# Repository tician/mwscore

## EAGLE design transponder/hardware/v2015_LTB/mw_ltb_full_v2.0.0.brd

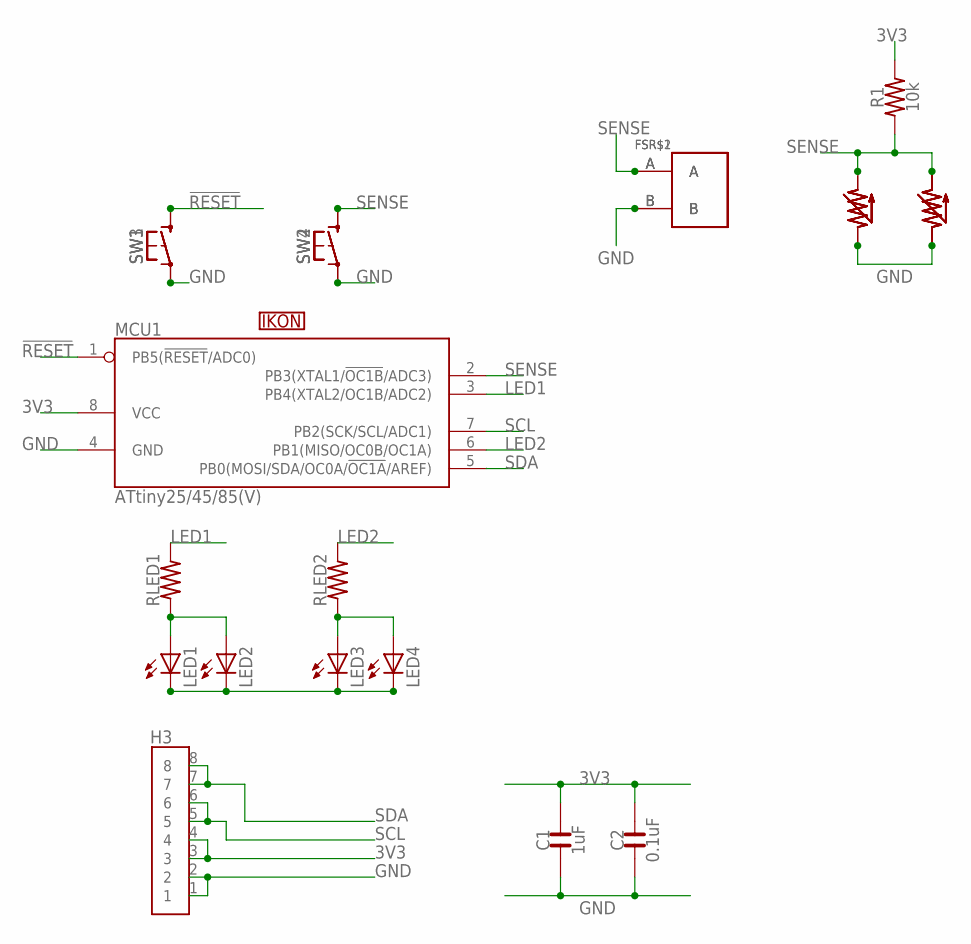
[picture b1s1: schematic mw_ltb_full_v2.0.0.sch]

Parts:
C1: 1uF; 0603_YAGEO
C2: 0.1uF; 0603_YAGEO
FSR$1, FSR$2: FSR_PAD88X44_P2B; FSR_PAD_88X44_P2B
H3: HEADER_8P-0.1"_2X4-SMD-SULLINS; HEADER-0.1"_2X4-SMD-SULLINS
LED1, LED2, LED3, LED4: LED-ZBEND_RM; Z-BEND_RM
MCU1: ATMEL_ATTINY25/45/85(V)-SOIC_DUAL; SOIC-8_DUAL
R1: 10k; 0603_YAGEO
RLED1, RLED2: RESISTOR-0603; 0603_YAGEO
SW1, SW2: SWITCH_SPST-KMT0; SWITCH_KMT0
SW3, SW4: SWITCH_SPST-TL3315; SWITCH_TL3315
U$1, U$3, U$9, U$10: FSR_PINS; FSR_0.1"-PITCH_PADS-0.05"X0.5"
U$2, U$4, U$5, U$6: FSR_PLACE; FSR_1.5[IN]_SQR
U$11: IKONLEARNING-20MIL; IKON_LEARNING_20MIL

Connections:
3V3: C1.2, C2.2, H3.3, H3.4, MCU1.8 (VCC), R1.2
!RESET: MCU1.1 (PB5(!RESET!/ADC0)), SW1.1@1 (1), SW1.1@2 (1), SW3.1@1 (1), SW3.1@2 (1)
GND: C1.1, C2.1, FSR$1.B, FSR$2.B, H3.1, H3.2, LED1.K (C), LED2.K (C), LED3.K (C), LED4.K (C), MCU1.4 (GND), SW1.2@1 (2), SW1.2@2 (2), SW2.2@1 (2), SW2.2@2 (2), SW3.2@1 (2), SW3.2@2 (2), SW4.2@1 (2), SW4.2@2 (2), U$1.P$1, U$3.P$2, U$9.P$2, U$10.P$1
LED1: MCU1.3 (PB4(XTAL2/OC1B/ADC2)), RLED1.2
LED2: MCU1.6 (PB1(MISO/OC0B/OC1A)), RLED2.2
unnamed: LED1.A, LED2.A, RLED1.1
unnamed: LED3.A, LED4.A, RLED2.1
SCL: H3.5, H3.6, MCU1.7 (PB2(SCK/SCL/ADC1))
SDA: H3.7, H3.8, MCU1.5 (PB0(MOSI/SDA/OC0A/!OC1A!/AREF))
SENSE: FSR$1.A, FSR$2.A, MCU1.2 (PB3(XTAL1/!OC1B!/ADC3)), R1.1, SW2.1@1 (1), SW2.1@2 (1), SW4.1@1 (1), SW4.1@2 (1), U$1.P$2, U$3.P$1, U$9.P$1, U$10.P$2

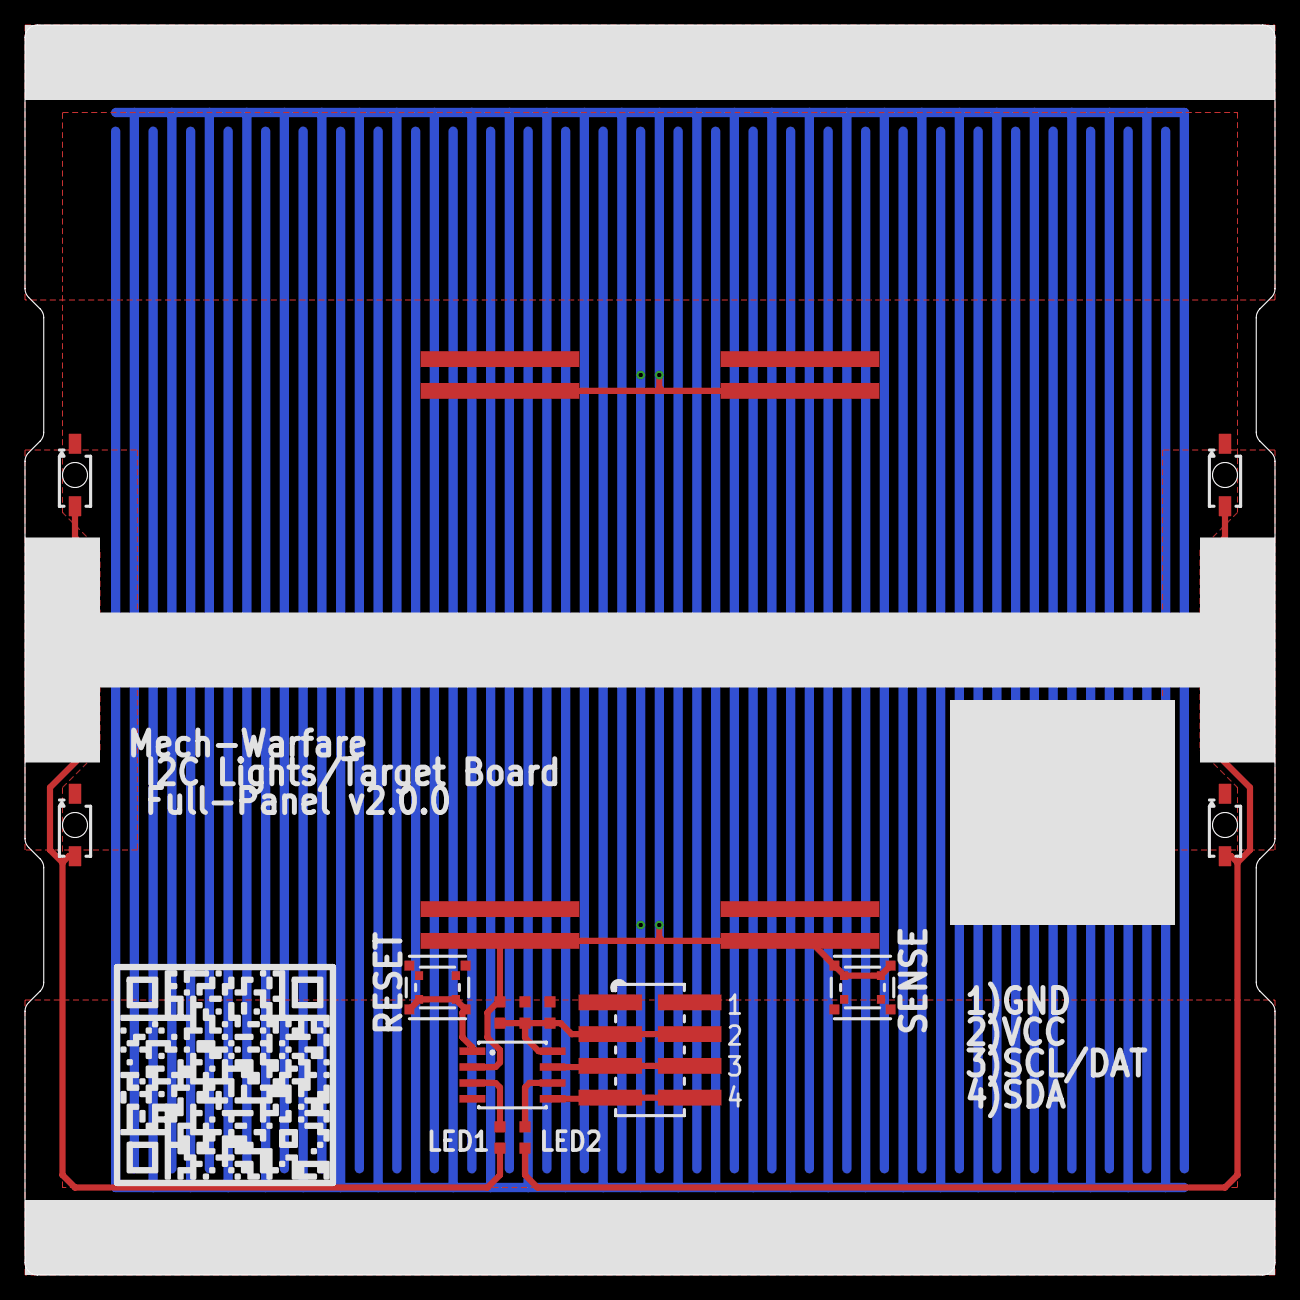
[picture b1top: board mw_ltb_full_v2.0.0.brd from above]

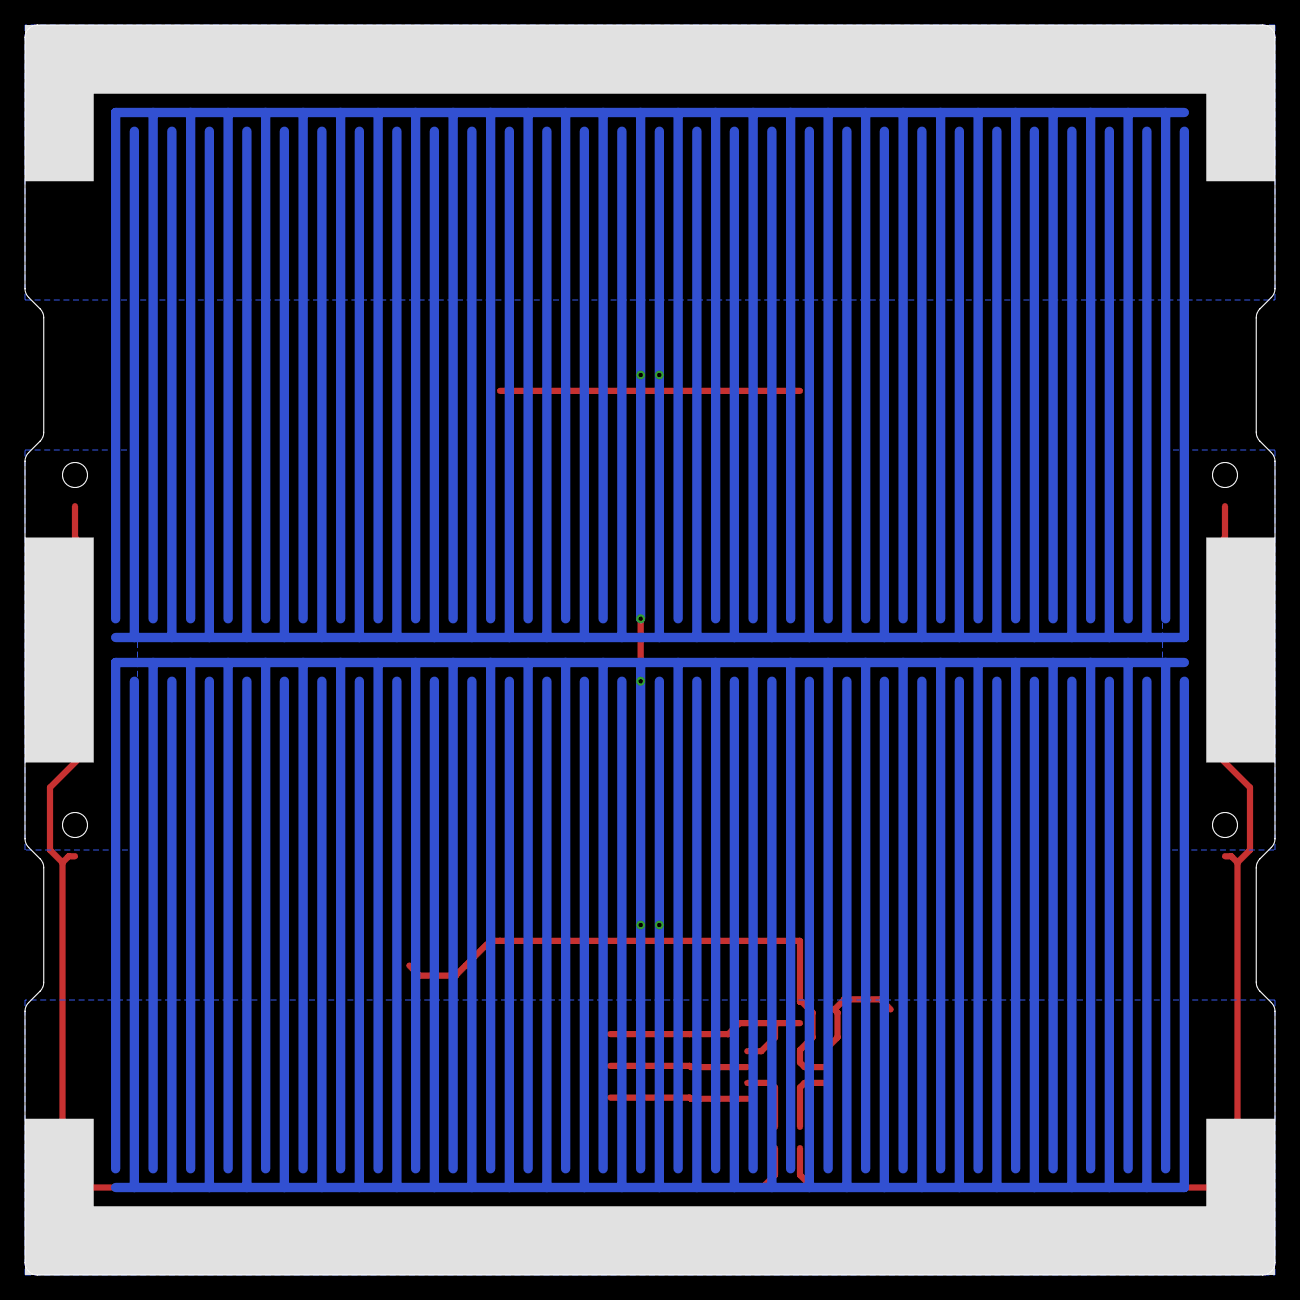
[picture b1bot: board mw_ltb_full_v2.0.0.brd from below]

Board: 2 copper layers, 100.0 x 100.0 mm, 26 parts (4 on the bottom side), 10 nets.

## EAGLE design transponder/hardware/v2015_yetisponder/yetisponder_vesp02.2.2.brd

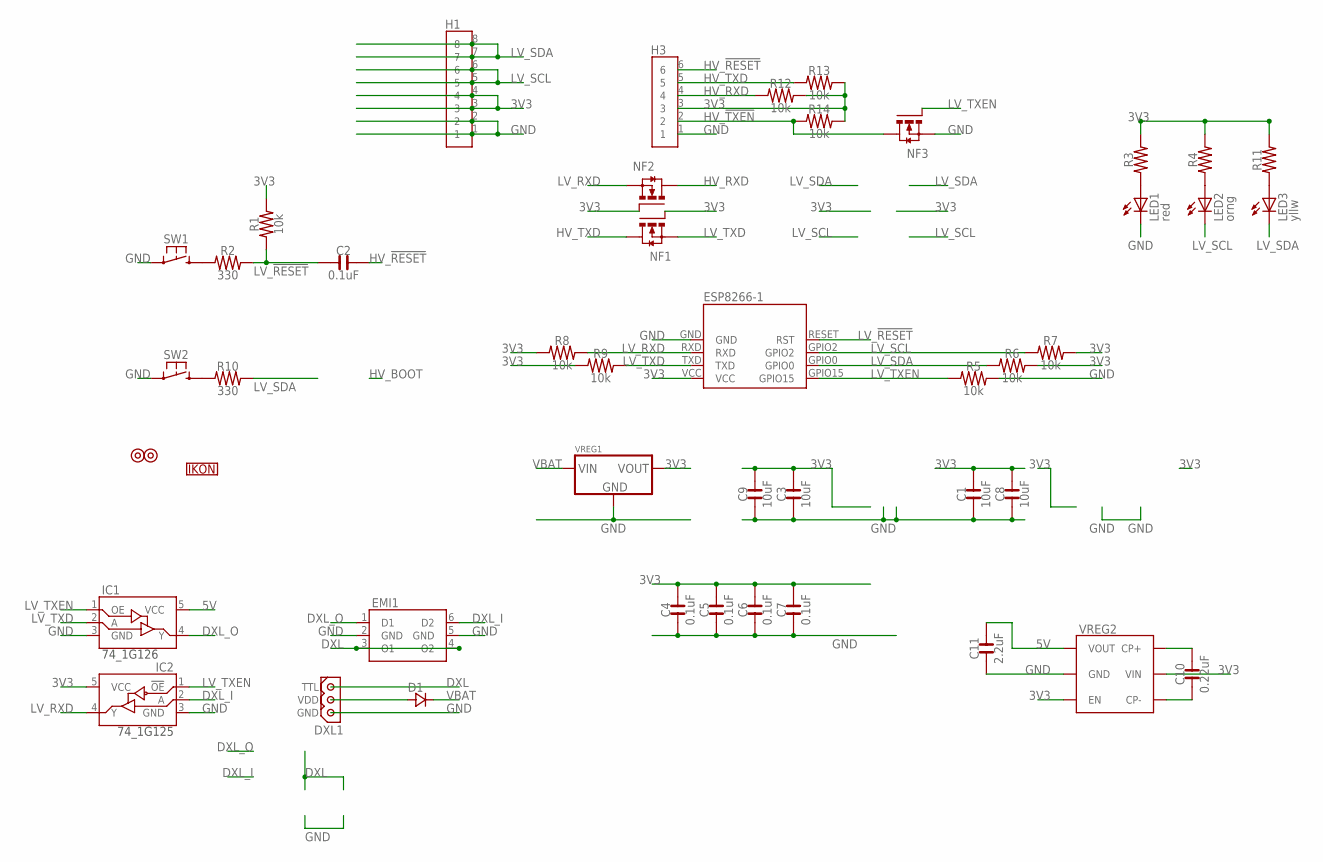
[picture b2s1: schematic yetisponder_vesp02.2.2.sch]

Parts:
C1, C3, C8, C9: 10uF; 0805_YAGEO
C2, C4, C5, C6, C7: 0.1uF; 0402_YAGEO
C10: 0.22uF; 0402_YAGEO
C11: 2.2uF; 0402_YAGEO
D1: DIODE_RECTIFIER-POWER-DI5; POWER-DI5
DXL1: DXL_TTL-V; MOLEX_5267-3
EMI1: EMI_2CH; SOT-563
ESP8266-1: ESP8266-02
H1: HEADER_8P-0.1"_2X4-SMD-SULLINS; HEADER-0.1"_2X4-SMD-SULLINS
H3: HEADER_6P-0.1"; HEADER-0.1"_1X6
IC1: LOGIC_74_1G126-DCK; DCK(R-PDSO-G5)_SC70
IC2: LOGIC_74_1G125-DCK; DCK(R-PDSO-G5)_SC70
IKON1: IKON-VERSACOMA-5; IKON_VERSACOMA_5MM
LED1: red; 0402_LED
LED2: orng; 0402_LED
LED3: yllw; 0402_LED
NF1, NF2, NF3: FET_N-CH-SOT-23-3; SOT-23-3
R1, R5, R6, R7, R8, R9, R12, R13, R14: 10k; 0402_YAGEO
R2, R10: 330; 0402_YAGEO
R3, R4, R11: RESISTOR-0402; 0402_YAGEO
S1, S2: METRIC_SCREWS-M2.5_T; M2.5_SCREW_TENTED
SW1, SW2: SWITCH_SPST-6MMX6MM-PTH; SWITCH_TE_1825910-7
VREG1: VREG_78XX-OKI-78SR-H; VREG-OKI-78SR-H
VREG2: VREG_REG710XX; SOT-23-6

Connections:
3V3: C1.2, C3.2, C4.2, C5.2, C6.2, C7.2, C8.2, C9.2, ESP8266-1.VCC, H1.3, H1.4, H3.3, IC2.5 (VCC), NF1.1G (G), NF2.1G (G), R1.2, R3.2, R4.2, R6.2, R7.2, R8.1, R9.1, R11.2, R12.2, R13.2, R14.2, VREG1.3 (VOUT), VREG2.3 (EN), VREG2.5 (VIN)
5V: C11.2, IC1.5 (VCC), VREG2.1 (VOUT)
DXL: DXL1.1 (TTL), EMI1.3 (O1), EMI1.4 (O2)
DXL_I: EMI1.6 (D2), IC2.2 (A)
DXL_O: EMI1.1 (D1), IC1.4 (Y)
GND: C1.1, C3.1, C4.1, C5.1, C6.1, C7.1, C8.1, C9.1, C11.1, DXL1.3 (GND), EMI1.2 (GND), EMI1.5 (GND), ESP8266-1.GND, H1.1, H1.2, H3.1, IC1.3 (GND), IC2.3 (GND), LED1.C, NF3.2S (S), R5.2, SW1.2@1 (2), SW1.2@2 (2), SW2.2@1 (2), SW2.2@2 (2), VREG1.2 (GND), VREG2.2 (GND)
HV_!RESET!: C2.2, H3.6
HV_!TXEN!: H3.2, NF3.3D (D), R14.1
HV_RXD: H3.4, NF2.3D (D), R12.1
HV_TXD: H3.5, NF1.3D (D), R13.1
LV_!RESET!: C2.1, ESP8266-1.RESET (RST), R1.1, R2.2
LV_RXD: ESP8266-1.RXD, IC2.4 (Y), NF2.2S (S), R8.2
LV_SCL: ESP8266-1.GPIO2, H1.5, H1.6, LED2.C, R7.1
LV_SDA: ESP8266-1.GPIO0, H1.7, H1.8, LED3.C, R6.1, R10.2
LV_TXD: ESP8266-1.TXD, IC1.2 (A), NF1.2S (S), R9.2
LV_TXEN: ESP8266-1.GPIO15, IC1.1 (OE), IC2.1 (!OE!), NF3.1G (G), R5.1
unnamed: R10.1, SW2.1@1 (1), SW2.1@2 (1)
unnamed: LED3.A, R11.1
unnamed: C10.2, VREG2.6 (CP+)
unnamed: D1.LEFT (A), D1.RIGHT (A), DXL1.2 (VDD)
unnamed: LED1.A, R3.1
unnamed: R2.1, SW1.1@1 (1), SW1.1@2 (1)
unnamed: LED2.A, R4.1
unnamed: C10.1, VREG2.4 (CP-)
VBAT: D1.PAD (C), VREG1.1 (VIN)

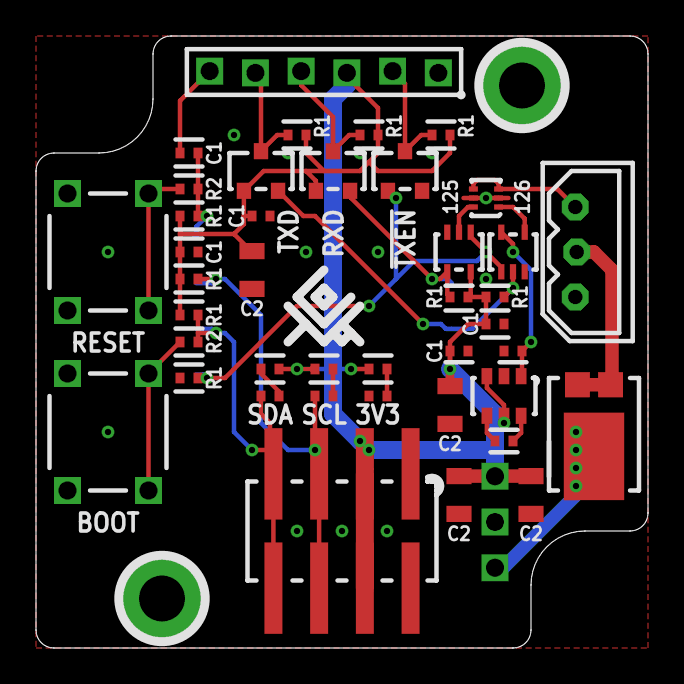
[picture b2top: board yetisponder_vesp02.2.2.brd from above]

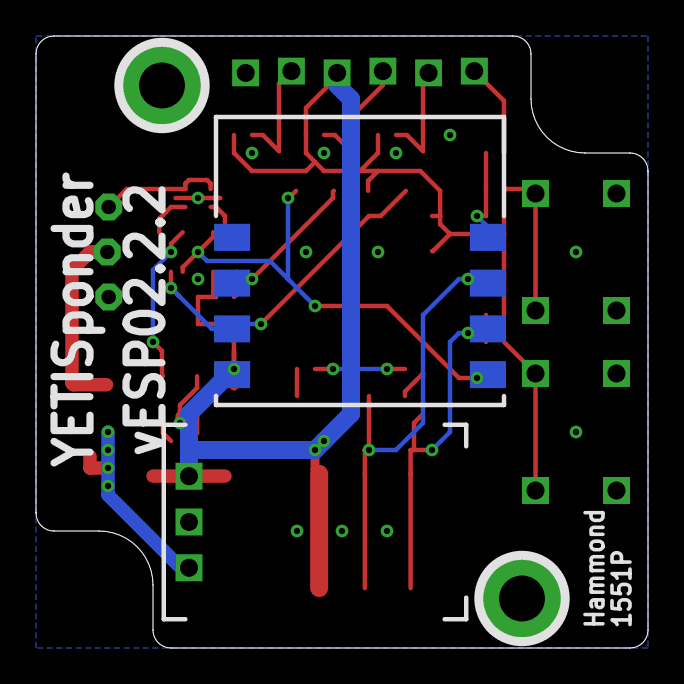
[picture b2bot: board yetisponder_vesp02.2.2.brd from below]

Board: 2 copper layers, 34.0 x 34.0 mm, 46 parts (2 on the bottom side), 25 nets.

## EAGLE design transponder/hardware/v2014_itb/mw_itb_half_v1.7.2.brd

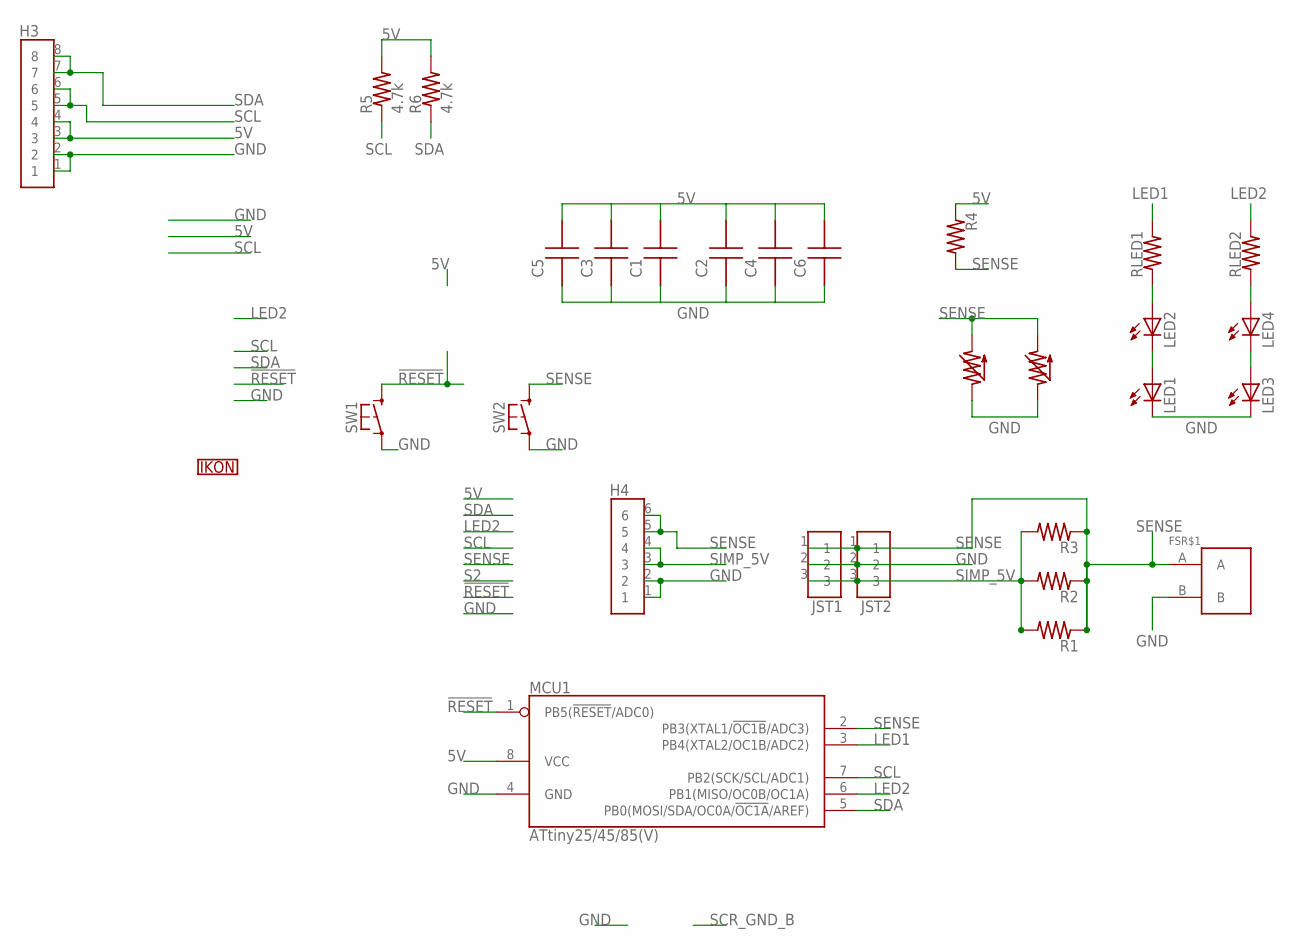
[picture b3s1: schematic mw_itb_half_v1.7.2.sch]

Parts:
C1, C2: CAPACITOR1206; 1206_YAGEO
C3, C4: CAPACITOR0805; 0805_YAGEO
C5, C6: CAPACITOR0603; 0603_YAGEO
FSR$1: FSR_PAD88X44_P2B; FSR_PAD_88X44_P2B
H3: HEADER_8P-0.1"_2X4-SMD-SULLINS; HEADER-0.1"_2X4-SMD-SULLINS
H4: HEADER_6P-0.1"_2X3-SMD-SULLINS; HEADER-0.1"_2X3-SMD-SULLINS
JST1, JST2: JST-3-PH-SMD-TOP; JST_PH_SMD_3_TOP
LED1, LED2, LED3, LED4: LED-ZBEND_RM; Z-BEND_RM
MCU1: ATMEL_ATTINY25/45/85(V)-SOIC_DUAL; SOIC-8_DUAL
R1: RESISTOR1206; 1206_YAGEO
R2: RESISTOR0805; 0805_YAGEO
R3, R4: RESISTOR0603; 0603_YAGEO
R5, R6: 4.7k; 0603_YAGEO
RLED1, RLED2: RESISTOR0603; 0603_YAGEO
SW1, SW2: SWITCH_SPST-KMT0; KMT0
U$5, U$6: FSR_PLACE; FSR_1.5[IN]_SQR
U$9, U$10: FSR_PINS; FSR_0.1"-PITCH_PADS-0.05"X0.5"
U$11: IKONLEARNING-20MIL; IKON_LEARNING_20MIL

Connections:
5V: C1.1, C2.1, C3.1, C4.1, C5.1, C6.1, H3.3, H3.4, MCU1.8 (VCC), R4.1, R5.2, R6.2
!RESET: MCU1.1 (PB5(!RESET!/ADC0)), SW1.1@1 (1), SW1.1@2 (1)
GND: C1.2, C2.2, C3.2, C4.2, C5.2, C6.2, FSR$1.B, H3.1, H3.2, H4.1, H4.2, JST1.2, JST2.2, LED1.K (C), LED3.K (C), MCU1.4 (GND), SW1.2@1 (2), SW1.2@2 (2), SW2.2@1 (2), SW2.2@2 (2), U$9.P$2, U$10.P$1
LED1: MCU1.3 (PB4(XTAL2/OC1B/ADC2)), RLED1.2
LED2: MCU1.6 (PB1(MISO/OC0B/OC1A)), RLED2.2
unnamed: LED2.A, RLED1.1
unnamed: LED1.A, LED2.K (C)
unnamed: LED4.A, RLED2.1
unnamed: LED3.A, LED4.K (C)
SCL: H3.5, H3.6, MCU1.7 (PB2(SCK/SCL/ADC1)), R5.1
SDA: H3.7, H3.8, MCU1.5 (PB0(MOSI/SDA/OC0A/!OC1A!/AREF)), R6.1
SENSE: FSR$1.A, H4.5, H4.6, JST1.1, JST2.1, MCU1.2 (PB3(XTAL1/!OC1B!/ADC3)), R1.1, R2.1, R3.1, R4.2, SW2.1@1 (1), SW2.1@2 (1), U$9.P$1, U$10.P$2
SIMP_5V: H4.3, H4.4, JST1.3, JST2.3, R1.2, R2.2, R3.2

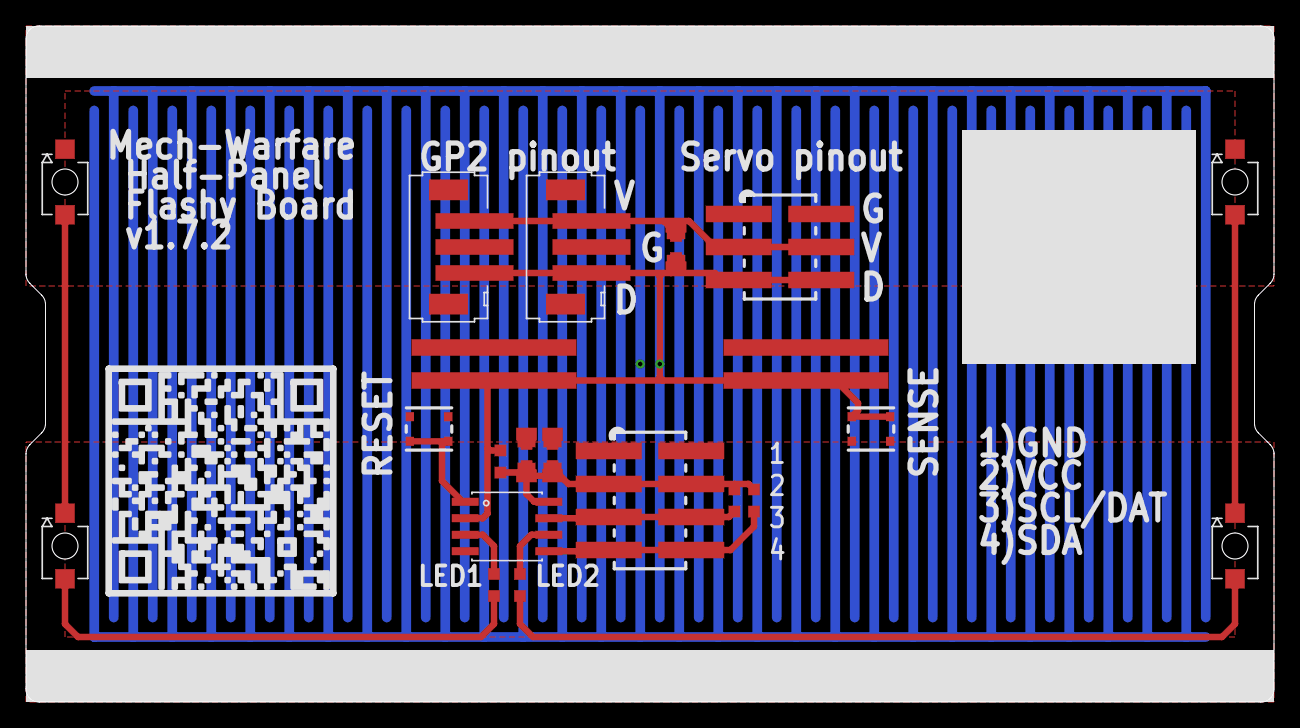
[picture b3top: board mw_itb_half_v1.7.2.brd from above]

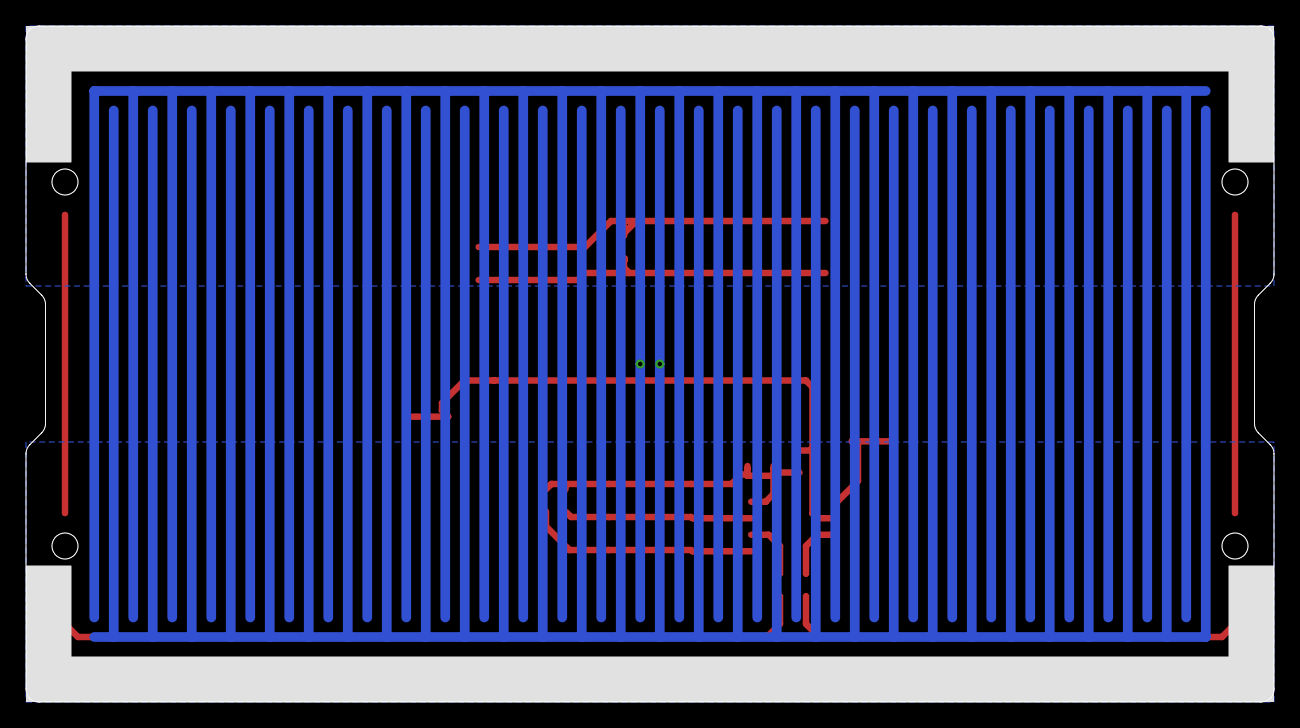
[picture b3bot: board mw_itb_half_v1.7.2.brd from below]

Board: 2 copper layers, 96.0 x 52.0 mm, 31 parts (2 on the bottom side), 13 nets.

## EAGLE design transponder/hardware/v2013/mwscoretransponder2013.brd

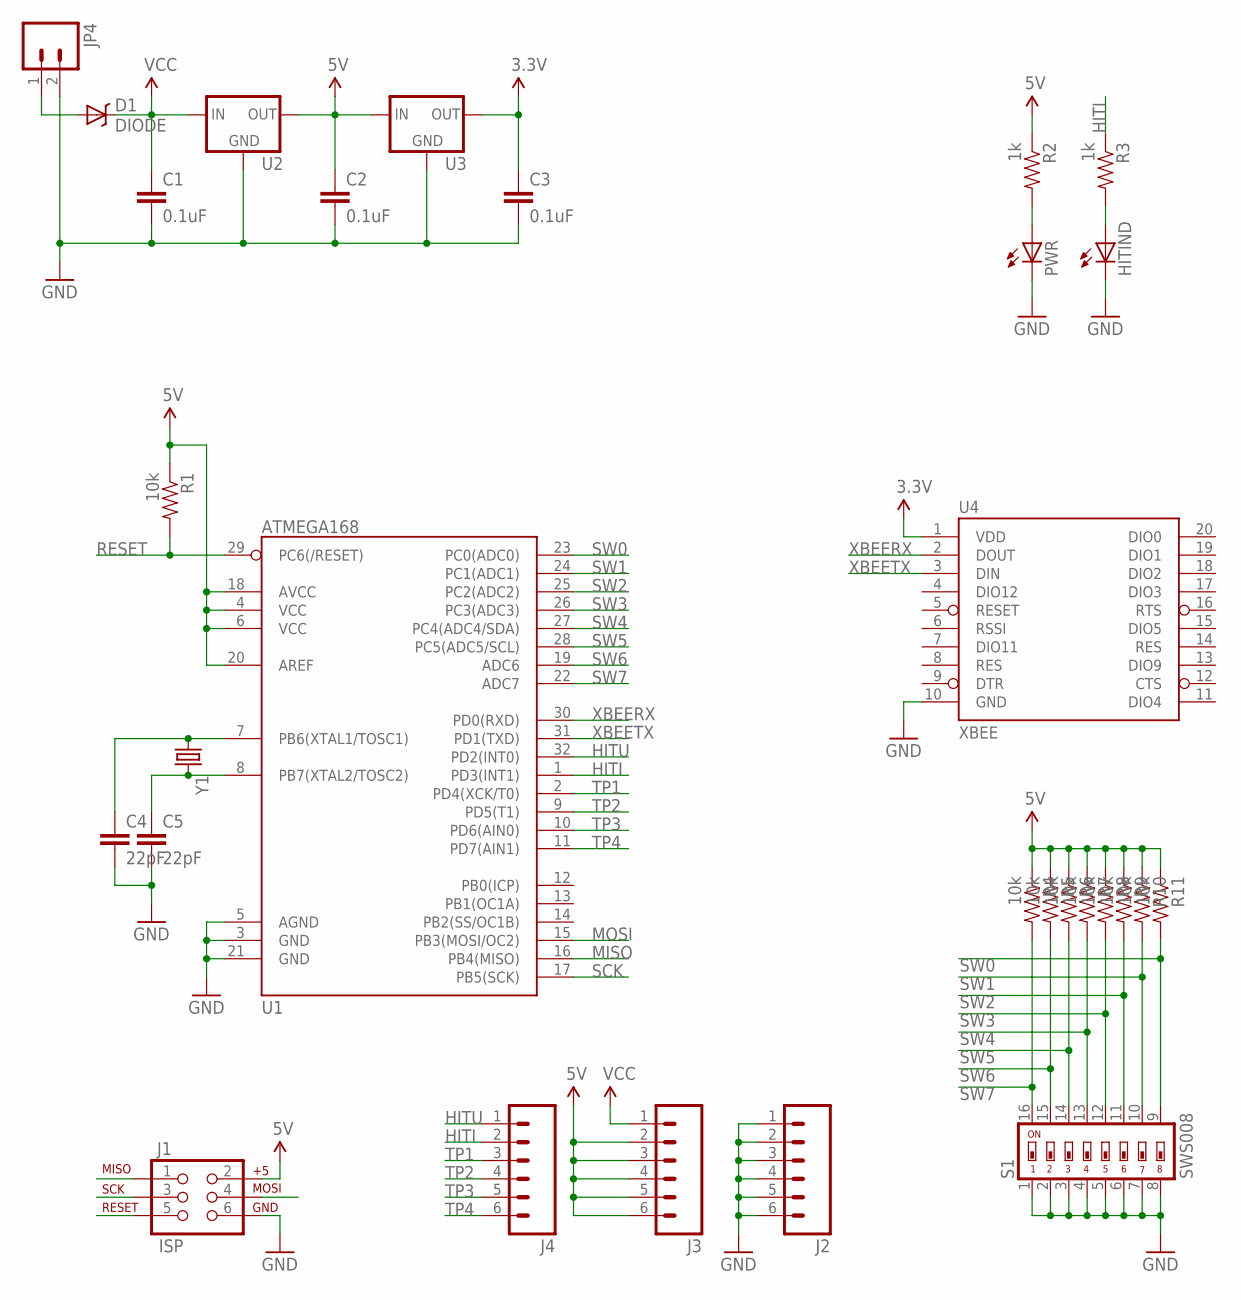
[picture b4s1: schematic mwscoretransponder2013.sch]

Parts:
C1, C2, C3: 0.1uF; 0603-CAP
C4, C5: 22pF; 0603-CAP
D1: DIODE; SMA-DIODE
HITIND: LED0603; LED-0603
J1: ISP; 2X3
J2, J3, J4: M06SIP; 1X06
JP4: M023.5MM_LOCK; SCREWTERMINAL-3.5MM-2_LOCK
PWR: LED0603; LED-0603
R1, R4, R5, R6, R7, R8, R9, R10, R11: 10k; 0603-RES
R2, R3: 1k; 0603-RES
S1: SWS008; SMS-008
U1: ATMEGA168; TQFP32-08
U2, U3: V_REG_MIC2920; SOT223
U4: XBEE; XBEE-SMD
Y1: CRYSTAL5X3; CRYSTAL-SMD-5X3

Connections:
3.3V: C3.1, U3.3 (OUT), U4.1 (VDD)
5V: C2.1, J1.2, J3.2, J3.3, J3.4, J3.5, J3.6, R1.1, R2.1, R4.1, R5.1, R6.1, R7.1, R8.1, R9.1, R10.1, R11.1, U1.4 (VCC), U1.6 (VCC), U1.18 (AVCC), U1.20 (AREF), U2.3 (OUT), U3.1 (IN)
GND: C1.2, C2.2, C3.2, C4.2, C5.2, HITIND.C, J1.6, J2.1, J2.2, J2.3, J2.4, J2.5, J2.6, JP4.2, PWR.C, S1.1, S1.2, S1.3, S1.4, S1.5, S1.6, S1.7, S1.8, U1.3 (GND), U1.5 (AGND), U1.21 (GND), U2.2 (GND), U3.2 (GND), U4.10 (GND)
HITI: J4.2, R3.1, U1.1 (PD3(INT1))
HITU: J4.1, U1.32 (PD2(INT0))
MISO: J1.1, U1.16 (PB4(MISO))
MOSI: J1.4, U1.15 (PB3(MOSI/OC2))
unnamed: PWR.A, R2.2
unnamed: HITIND.A, R3.2
unnamed: C4.1, U1.7 (PB6(XTAL1/TOSC1)), Y1.1
unnamed: D1.A, JP4.1
unnamed: C5.1, U1.8 (PB7(XTAL2/TOSC2)), Y1.3 (2)
RESET: J1.5, R1.2, U1.29 (PC6(/RESET))
SCK: J1.3, U1.17 (PB5(SCK))
SW0: R11.2, S1.9, U1.23 (PC0(ADC0))
SW1: R10.2, S1.10, U1.24 (PC1(ADC1))
SW2: R9.2, S1.11, U1.25 (PC2(ADC2))
SW3: R8.2, S1.12, U1.26 (PC3(ADC3))
SW4: R7.2, S1.13, U1.27 (PC4(ADC4/SDA))
SW5: R6.2, S1.14, U1.28 (PC5(ADC5/SCL))
SW6: R5.2, S1.15, U1.19 (ADC6)
SW7: R4.2, S1.16, U1.22 (ADC7)
TP1: J4.3, U1.2 (PD4(XCK/T0))
TP2: J4.4, U1.9 (PD5(T1))
TP3: J4.5, U1.10 (PD6(AIN0))
TP4: J4.6, U1.11 (PD7(AIN1))
VCC: C1.1, D1.C, J3.1, U2.1 (IN)
XBEERX: U1.30 (PD0(RXD)), U4.2 (DOUT)
XBEETX: U1.31 (PD1(TXD)), U4.3 (DIN)

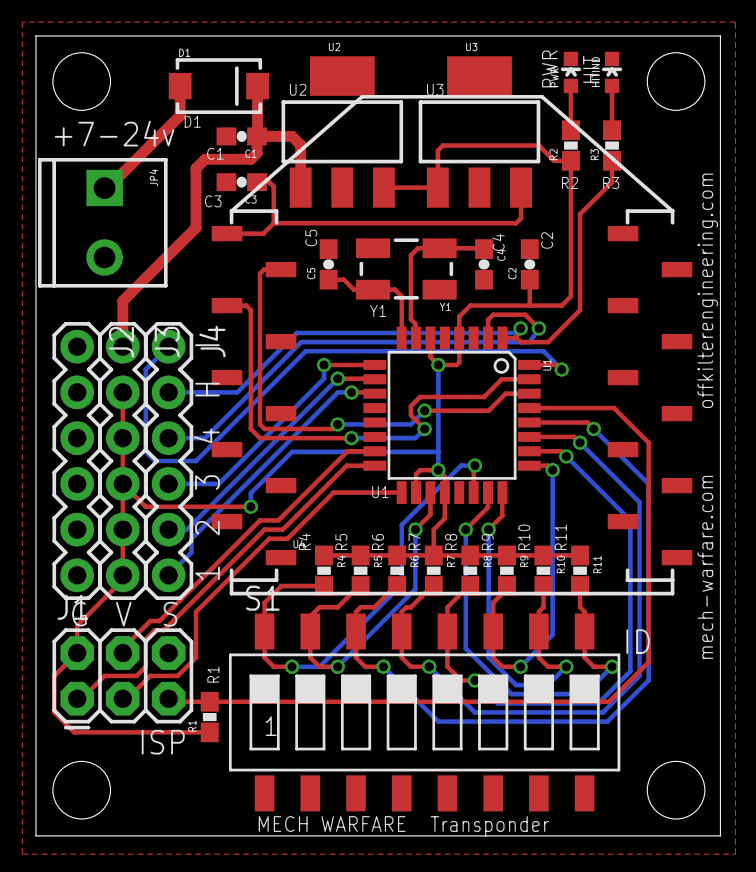
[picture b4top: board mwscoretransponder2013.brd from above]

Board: 2 copper layers, 38.0 x 44.4 mm, 30 parts (0 on the bottom side), 29 nets.

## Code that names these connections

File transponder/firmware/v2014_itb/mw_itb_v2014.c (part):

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///~~~~~~~~~~~~~~~~~~~~~~~~~~~~~~~~~~~~~~~~~~~~~~~~~~~~~~~~~~~~~~~~~~~~~~~~~~~~~
/// PIN DEFINITIONS
///~~~~~~~~~~~~~~~~~~~~~~~~~~~~~~~~~~~~~~~~~~~~~~~~~~~~~~~~~~~~~~~~~~~~~~~~~~~~~
	PB0 - I/O - SDA												DIP-P5	MOSI
	PB1 - OUT - LED2 -	Pin : 62[Ohm] : [>] : [>] : GND			DIP-P6	MISO
	PB2 - I/O - DATA/SCL										DIP-P7	SCK
	PB3 - ADC - BUTTON/SENSE (ADC3)								DIP-P2
	PB4 - OUT - LED1 -	Pin : 62[Ohm] : [>] : [>] : GND			DIP-P3
	PB5 - N/A - RESET											DIP-P1	!RESET
///~~~~~~~~~~~~~~~~~~~~~~~~~~~~~~~~~~~~~~~~~~~~~~~~~~~~~~~~~~~~~~~~~~~~~~~~~~~~~
*/
#define LED1_OFF()	{PORTB &=~(1<<PIN4);}
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	conti_table[3] = eeprom_read_byte(&eep_fsr_threshold);

///~~~~~~~~~~~~~~~~~~~~~~~~~~~~~~~~~~~~~~~~~~~~~~~~~~~~~~~~~~~~~~~~~~~~~~~~~~~~~
	// Set PB4 and PB1 output (LED outputs enabled)
	DDRB = (1<<PIN1) | (1<<PIN4);
	// Set PB4 and PB1 low (LEDs OFF)
	PORTB &= ~((1<<PIN1) | (1<<PIN4));
	// Disable PB3/ADC3 pull-up (use 10k external pull-up)
	PORTB &= ~(1<<PIN3);

///~~~~~~~~~~~~~~~~~~~~~~~~~~~~~~~~~~~~~~~~~~~~~~~~~~~~~~~~~~~~~~~~~~~~~~~~~~~~~
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
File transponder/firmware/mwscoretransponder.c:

/*
	MWScore Transponder
	
	XBEE setup:
	ATBD = 5 (38400bps)
	ATID = 6200
	MY   = 6200 + TRANSPONDER_ID
	DL   = 6201
	CH   = c
	
	ATMEGA168P Fuse Setting:
	avrdude -P usb -c avrispmkII -p amega168 -F -U lfuste:w:0xce:m -U hfuse:w:0xdf:m -U efuse:w:0xf9:m

	To Program:
	> make
	> make program
*/
 
 
#include <avr/io.h>
#include <avr/interrupt.h>
#include <util/delay.h>

#define TRANSPONDER_ID 43

#define XBEE_BAUDRATE 38400

#define PANEL1 2
#define PANEL2 4
#define PANEL3 8
#define PANEL4 16

#define MS_COOLDOWN 1000
#define MS_SIGNAL 50

#define LED_RATE 50
#define LED_PERIOD 300 // LED_RATE * 6

volatile uint8_t hit = 0;

ISR(PCINT1_vect)
{
	hit = PINC;
}

void tx(uint8_t c)
{
	while(bit_is_clear(UCSR0A, UDRE0));
	UDR0 = c;
}

int main(void)
{
	uint32_t delay = 0;
	uint8_t panel = 0;

	// xbee init
	UBRR0H  = ((F_CPU / 16 + XBEE_BAUDRATE / 2) / XBEE_BAUDRATE - 1) >> 8;
	UBRR0L  = ((F_CPU / 16 + XBEE_BAUDRATE / 2) / XBEE_BAUDRATE - 1);
	UCSR0B |= (1 << TXEN0);
	
	// panel inputs
	DDRC &= ~(1 << PC1);
	DDRC &= ~(1 << PC2);
	DDRC &= ~(1 << PC3);
	DDRC &= ~(1 << PC4);
	
	// led outputs
	DDRC |=  (1 << PC0);
	DDRC |=  (1 << PC5);
	
	// Pin change interrupt 1 enabled. Any change on enabled PCINT13..10 will cause and interupt.
	PCICR  |= (1 << PCIE1);
	PCMSK1 |= (1 << PCINT9);  // PC1
	PCMSK1 |= (1 << PCINT10); // PC2
	PCMSK1 |= (1 << PCINT11); // PC3
	PCMSK1 |= (1 << PCINT12); // PC4
	
	// enable interups
	sei();
	
	while(1)
	{
		if(hit > 0)
		{
		
			// determine panel that was hit
			if      (!(hit & PANEL1)) { delay = MS_SIGNAL * 1; panel = 1; }
			else if (!(hit & PANEL2)) { delay = MS_SIGNAL * 2; panel = 2; }
			else if (!(hit & PANEL3)) { delay = MS_SIGNAL * 3; panel = 3; }
			else                      { delay = MS_SIGNAL * 4; panel = 4; }
			
			// hit output high
			PORTC &= ~(1 << PC0);

			// tx hit packet			
			tx((uint8_t) 0x55);
			tx((uint8_t) TRANSPONDER_ID);
			tx((uint8_t) (255 - TRANSPONDER_ID));
			tx((uint8_t) panel);
			
			// delay and reset hit output
			_delay_ms(delay);
			PORTC |=  (1 << PC0);
			
			// blink LED board 3 times
			for (int x = 0; x < 3; x++)
			{
				PORTC |=  (1 << PC5);
				_delay_ms(LED_RATE);
				PORTC &= ~(1 << PC5);
				_delay_ms(LED_RATE);
			}
			
			// delay for the remaining cooldown period
			_delay_ms(MS_COOLDOWN - LED_PERIOD - delay);
			
			// reset variables
			hit = 0;
			delay = 0;
			panel = 0;
		}
	}

	return 0;
}

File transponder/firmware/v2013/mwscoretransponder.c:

/*
	MWScore Transponder
	
	XBEE setup:
	ATBD = 5 (38400bps)
	ATID = 6200
	MY   = 6200 + TRANSPONDER_ID
	DL   = 6201
	CH   = c
	
	ATMEGA328 Fuse Setting:
	$ sudo avrdude -P usb -c avrispmkII -p m328p -B 100 -F -U lfuse:w:0xce:m -U hfuse:w:0xdf:m -U efuse:w:0xff:m

	To Program:
	$ sudo make program
*/ 
 
#include <avr/io.h>
#include <avr/interrupt.h>
#include <util/delay.h>

#define XBEE_BAUDRATE 38400

#define PANELMASK  240
#define PANEL1     112
#define PANEL2     176
#define PANEL3     208
#define PANEL4     224

#define MS_COOLDOWN 1000
#define MS_SIGNAL 50

#define LED_RATE 50
#define LED_PERIOD 300 // LED_RATE * 6

volatile uint8_t hit = 0;

ISR(PCINT2_vect)
{
	hit = PIND;
}

void delay_ms(uint16_t count) {
  while(count--) {
    _delay_ms(1);
  }
} 

void tx(uint8_t c)
{
	while(bit_is_clear(UCSR0A, UDRE0));
	UDR0 = c;
}

int main(void)
{
	uint32_t delay = 0;
	uint8_t panel = 0;
	uint8_t id;

	// xbee init
	UBRR0H  = ((F_CPU / 16 + XBEE_BAUDRATE / 2) / XBEE_BAUDRATE - 1) >> 8;
	UBRR0L  = ((F_CPU / 16 + XBEE_BAUDRATE / 2) / XBEE_BAUDRATE - 1);
	UCSR0B |= (1 << TXEN0);
	
	// panel inputs
	DDRD &= ~(1 << PD4);
	DDRD &= ~(1 << PD5);
	DDRD &= ~(1 << PD6);
	DDRD &= ~(1 << PD7);
	
	// id inputs
	DDRC = 0;
	
	// led outputs
	DDRD |= (1 << PD2);
	DDRD |= (1 << PD3);
	
	// Pin change interrupt 1 enabled. Any change on enabled PCINT23..16 will cause and interupt.
	PCICR  |= (1 << PCIE2);
	PCMSK2 |= (1 << PCINT20);
	PCMSK2 |= (1 << PCINT21);
	PCMSK2 |= (1 << PCINT22);
	PCMSK2 |= (1 << PCINT23);
	
	// enable interups
	sei();
	
	while(1)
	{
		if(hit != 0)
		{		
			// determine panel that was hit
			if      ((hit & PANELMASK) == PANEL1) { delay = MS_SIGNAL * 1; panel = 1; }
			else if ((hit & PANELMASK) == PANEL2) { delay = MS_SIGNAL * 2; panel = 2; }
			else if ((hit & PANELMASK) == PANEL3) { delay = MS_SIGNAL * 3; panel = 3; }
			else if ((hit & PANELMASK) == PANEL4) { delay = MS_SIGNAL * 4; panel = 4; }
			else                                  { delay = MS_SIGNAL * 5; panel = 5; }
			
			if(panel != 0)
			{			
				// hit output high
				PORTD |= (1 << PD3);

				// tx hit packet
				id = 63 - (0x3f & PINC);
				tx((uint8_t) 0x55);
				tx((uint8_t) id);
				tx((uint8_t) (0xff - id));
				tx((uint8_t) panel);
			
				// delay and reset hit output
				delay_ms(delay);
				PORTD &= ~(1 << PD3);
			
				// blink LED board 3 times
				for (int x = 0; x < 3; x++)
				{
					PORTD |=  (1 << PD2);
					delay_ms(LED_RATE);
					PORTD &= ~(1 << PD2);
					delay_ms(LED_RATE);
				}
			
				// delay for the remaining cooldown period
				delay_ms(MS_COOLDOWN - LED_PERIOD - delay);
			}
			
			// reset variables
			hit = 0;
			delay = 0;
			panel = 0;
		}
	}

	return 0;
}

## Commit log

2012-07-05 moved transponder hardware in version dirs
2012-07-05 started v2013 hardware schematic
2012-07-05 init part selection and board layout
2012-10-20 added support for DLink 930 camera
2012-12-08 v2013 firmware
2012-12-09 panel masking corrected
2012-12-13 H and I outputs swapped
2012-12-13 case for multiple hits detected added
2013-02-26 final 2013 firmware
2013-08-06 Initial Commit
    Revised 2013 version, includes gerbers & DXFs for stencils.
2014-11-29 Ordered 10 full-panel boards with ENIG finish from Seeed on 2014-11-29, but will not arrive until late December to mid January for testing. Trace FSR is in the same footprint used to mount two 1.5" F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
2015-01-08 Small updates to mw_itb design files. Basically changed silkscreen for LEDs and added additional button footprint for slightly larger and significantly less expensive TL3315 pushbuttons from E-Switch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
2015-06-03 finally added source and bom for ITB. nansponder is getting complete overhaul to ESP8266-02 module for arduino-1.6 instead of xbee and ATmega328p arduino.
2015-06-03 esp8266 nansponder.
2015-06-09 bit more work on sponder. need reboot.
2015-06-14 derpity derp derp. forgot to checkout esp8266 branch. lots of work, not likely to work.
2015-06-14 bit more on mwUDP
2015-06-17 bit more.
2015-06-23 YETIS - YET another 'Intelligent' Score System for Mech Warfare
2015-06-23 renamed YETIS files
2015-06-24 bleh.
2015-06-24 grr.
2015-06-24 cleanup for YETIS.
2015-06-25 still need to put LED under control of timer1.
2015-06-26 maybe working?
2015-06-26 blah.
2015-06-26 woof
2015-06-26 fixed makefile?
2015-06-26 still not building. udef refs to usiTwi functions. something stupid on my part, no doubt.
2015-06-26 no extern 'C' in usiTwiSlave.h. now to test with hardware. might just sacrifice an old soldering iron tip to make the stencil...
2015-06-26 still haven't made a stencil to assemble the LTB or YETIS-ponder yet, but did file one of the many spare iron tips to a nice point that should be useful for melting the UHMW-PE film and then doing fi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
2015-06-27 still no hardware test.
2015-06-28 still figuring out how to make LED states update correctly.
2015-06-28 possibly functional, but still no hardware test yet.
2015-06-28 still no hardware test. definitely breaking it into smaller pieces/files once I get it to a known working state.
2015-06-28 still no hardware tests.
2015-07-02 pluh.assembled one board, but no luck yet.
2015-07-02 doh. hopefully the sei() will fix the timers.
2015-07-02 Have finally gotten timer0 and timer1 working, but main code of loop() not working yet and I2C untested.
2015-07-02 such an idiot. flipped indices for fsr-sense-limit and consecutive-senses-per-hit.
2015-07-02 cleaned up old commented code
2015-07-03 renamed and changed license
2015-07-04 sort of working...
2015-07-09 still not working correctly
2015-10-16 attempting to add dxl device (and/or pass-through) to dxl20
2015-10-17 finishing big backup and reboot, then cleanout.
2016-01-31 added yetis transponder
2016-03-13 some renaming for arduino
2016-06-22 derp
2016-06-22 slightly reworked traces to put LEDs in parallel to enable operation off of a 3.3V supply.

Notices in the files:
transponder/firmware/v2014_itb/mw_itb_v2014.c:
Copyright (c) 2012, 2013, 2014, 2015 Matthew Paulishen. All rights reserved.
This program is free software: you can redistribute it and/or modify
it under the terms of the GNU General Public License as published by
the Free Software Foundation, either version 3 of the License, or
(at your option) any later version.
parts and their libraries:
SparkFun: Licensing: CC v3.0 Share-Alike You are welcome to use this library for commercial purposes.
